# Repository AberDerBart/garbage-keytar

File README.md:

# garbage-keytar

Code and design for a keytar made from an old PC keyboard

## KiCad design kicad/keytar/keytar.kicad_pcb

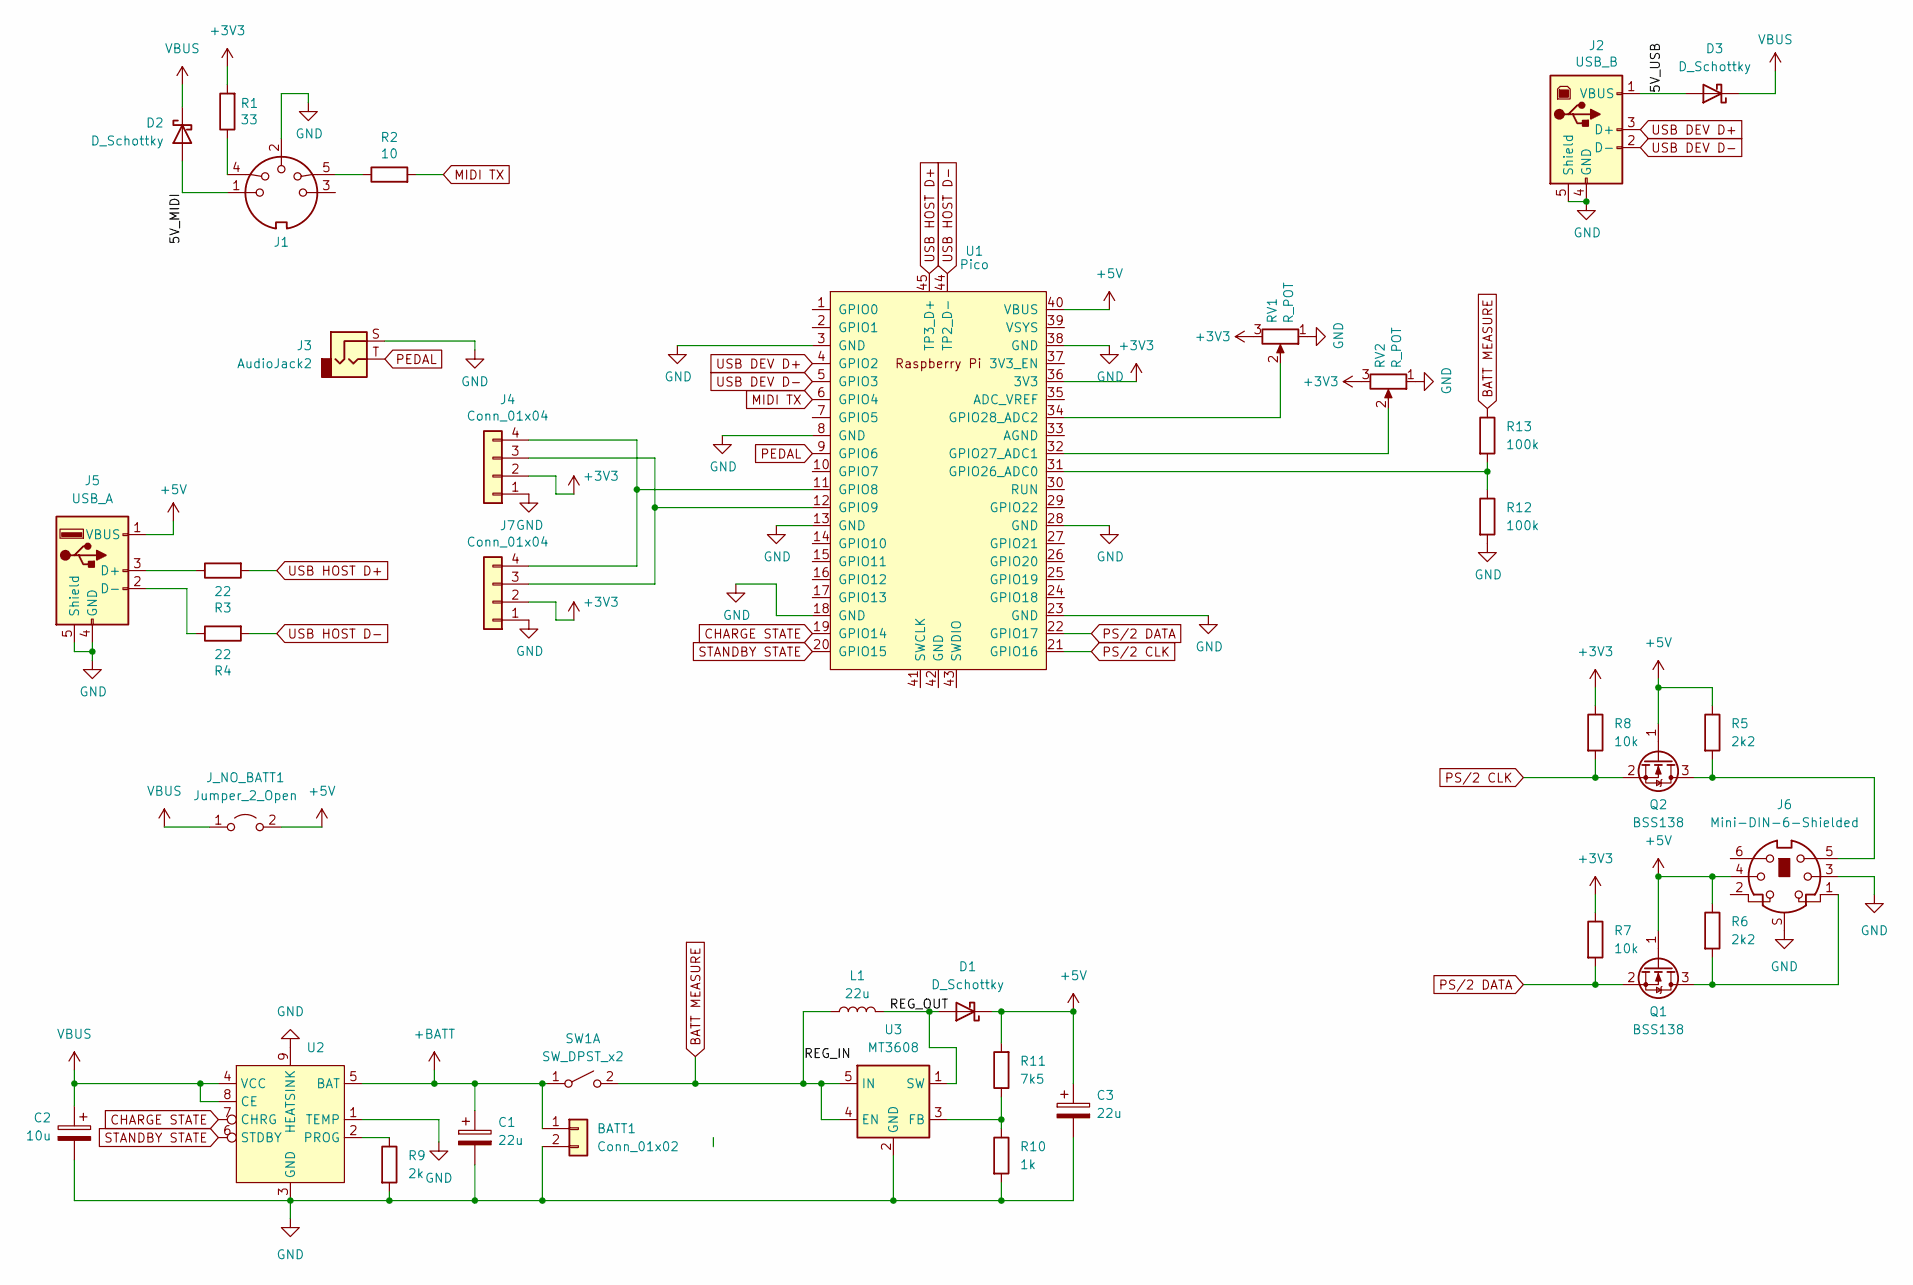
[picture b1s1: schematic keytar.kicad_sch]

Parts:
BATT1: Conn_01x02; JST_XH_B2B-XH-A_1x02_P2.50mm_Vertical
C1, C3: 22u; CP_Elec_4x5.3
C2: 10u; CP_Elec_4x5.3
D1, D2, D3: D_Schottky; D_SMA
J1: MIDI_DIN5
J2: USB_B; USB_B_OST_USB-B1HSxx_Horizontal
J3: AudioJack2; Jack_6.35mm_Neutrik_NRJ4HF_Horizontal
J4, J7: Conn_01x04; JST_XH_B4B-XH-A_1x04_P2.50mm_Vertical
J5: USB_A; USB_A_Molex_67643_Horizontal
J6: Mini-DIN-6-Shielded; EB-DIOS M06
J_NO_BATT1: Jumper_2_Open; SolderJumper-2_P1.3mm_Open_RoundedPad1.0x1.5mm
L1: 22u; L_Bourns-SRN4018
Q1, Q2: BSS138; SOT-23
R1: 33; R_1206_3216Metric_Pad1.30x1.75mm_HandSolder
R2: 10; R_1206_3216Metric_Pad1.30x1.75mm_HandSolder
R3, R4: 22; R_1206_3216Metric_Pad1.30x1.75mm_HandSolder
R5, R6: 2k2; R_1206_3216Metric_Pad1.30x1.75mm_HandSolder
R7, R8: 10k; R_1206_3216Metric_Pad1.30x1.75mm_HandSolder
R9: 2k; R_1206_3216Metric_Pad1.30x1.75mm_HandSolder
R10: 1k; R_1206_3216Metric_Pad1.30x1.75mm_HandSolder
R11: 7k5; R_1206_3216Metric_Pad1.30x1.75mm_HandSolder
R12, R13: 100k; R_1206_3216Metric_Pad1.30x1.75mm_HandSolder
RV1, RV2: R_POT; JST_XH_B3B-XH-A_1x03_P2.50mm_Vertical
SW1: SW_DPST_x2; JST_XH_B3B-XH-A_1x03_P2.50mm_Vertical
U1: Pico; RPi_Pico_debug_hole_USB_SMD_TH
U2: HSOP-8-1EP_3.9x4.9mm_P1.27mm_EP2.3x2.3mm
U3: MT3608; SOT-23-6

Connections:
+3V3: J4.2, J7.2, R1.2, R7.1, R8.1, RV1.3, RV2.3, U1.36 (3V3)
+5V: C3.1, D1.1 (K), J5.1 (VBUS), J6.4, J_NO_BATT1.2 (B), Q1.1 (G), Q2.1 (G), R5.1, R6.1, R11.2, U1.40 (VBUS)
+BATT: BATT1.1, C1.1, SW1.1 (A), U2.5 (BAT)
/5V_MIDI: D2.2 (A), J1.1
/5V_USB: D3.2 (A), J2.1 (VBUS)
/REG_OUT: D1.2 (A), L1.2, U3.1 (SW)
BATT MEASURE: L1.1, R13.1, SW1.2 (B), U3.4 (EN), U3.5 (IN)
CHARGE STATE: U1.19 (GPIO14), U2.7 (CHRG)
GND: BATT1.2, C1.2, C2.2, C3.2, J1.2, J2.4 (GND), J2.5 (Shield), J3.S, J4.1, J5.4 (GND), J5.5 (Shield), J6.3, J6.S, J7.1, R9.2, R10.2, R12.2, RV1.1, RV2.1, U1.3 (GND), U1.8 (GND), U1.13 (GND), U1.18 (GND), U1.23 (GND), U1.28 (GND), U1.38 (GND), U2.1 (TEMP), U2.3 (GND), U2.9 (HEATSINK), U3.2 (GND)
MIDI TX: R2.2, U1.6 (GPIO4)
unnamed: J1.4, R1.1
unnamed: J1.5, R2.1
unnamed: J4.3, J7.3, U1.12 (GPIO9)
unnamed: J4.4, J7.4, U1.11 (GPIO8)
unnamed: J5.3 (D+), R3.1
unnamed: J5.2 (D-), R4.1
unnamed: J6.1, Q1.3 (D), R6.2
unnamed: J6.5, Q2.3 (D), R5.2
unnamed: R12.1, R13.2, U1.31 (GPIO26_ADC0)
unnamed: RV2.2, U1.32 (GPIO27_ADC1)
unnamed: RV1.2, U1.34 (GPIO28_ADC2)
unnamed: R9.1, U2.2 (PROG)
unnamed: R10.1, R11.1, U3.3 (FB)
PEDAL: J3.T, U1.9 (GPIO6)
PS/2 CLK: Q2.2 (S), R8.2, U1.21 (GPIO16)
PS/2 DATA: Q1.2 (S), R7.2, U1.22 (GPIO17)
STANDBY STATE: U1.20 (GPIO15), U2.6 (STDBY)
USB DEV D+: J2.3 (D+), U1.4 (GPIO2)
USB DEV D-: J2.2 (D-), U1.5 (GPIO3)
USB HOST D+: R3.2, U1.45 (TP3_D+)
USB HOST D-: R4.2, U1.44 (TP2_D-)
VBUS: C2.1, D2.1 (K), D3.1 (K), J_NO_BATT1.1 (A), U2.4 (VCC), U2.8 (CE)

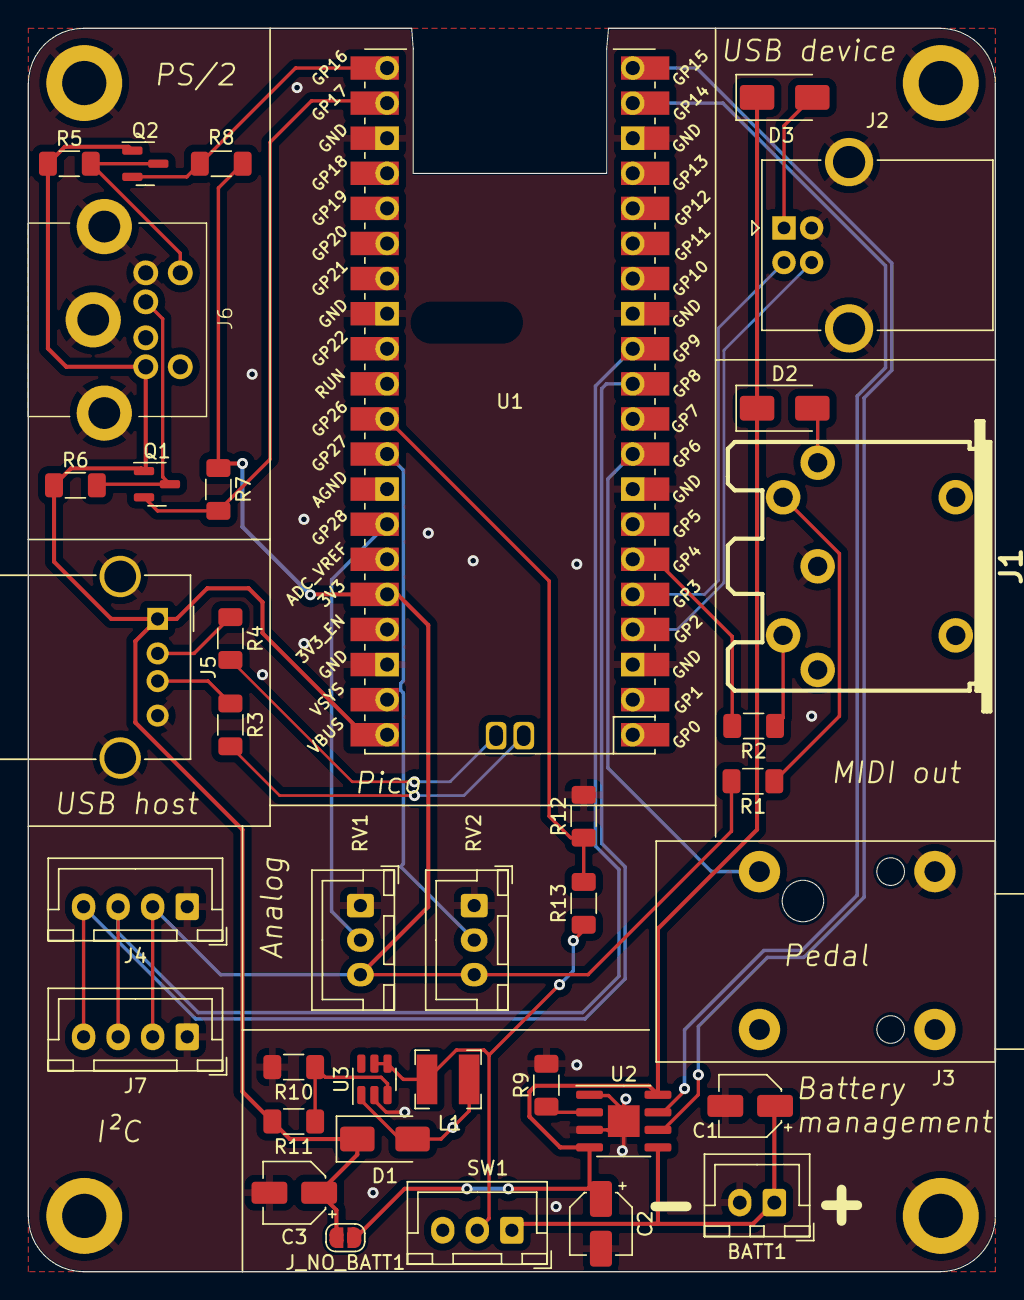
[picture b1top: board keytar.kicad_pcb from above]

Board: 2 copper layers, 70.0 x 90.0 mm, 37 parts (0 on the bottom side), 32 nets.

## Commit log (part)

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2021-04-21 implement MIDI via serial
2021-04-21 implement usb host
2021-04-21 combine keyboard and midi
2021-04-21 implement noteoff events
2021-04-23 add pico_sdk_import
2021-04-24 cad numblock cover
2021-04-24 add makefile
2021-04-24 implement control values with potentiometers
2021-04-24 add gitignore
2021-04-24 add openocd to shell.nix
2021-04-24 cleanup
2021-04-24 improve control value debounce
2021-04-24 rename main source file and binary
2021-04-24 add < key
2021-06-13 improve case
2021-08-19 use pico-sdk in submodule
2021-08-19 re-activate pitchbend
2021-08-19 add pcb
2021-08-19 only report pitchbend on change
2021-09-05 add pico-ssd1306 submodule
2021-09-05 disabled control values
2021-09-05 WIP: adjust pitchbend
2021-09-05 WIP: adapt shell.nix to nixos 21.05
2021-09-05 properly implement PCB
2021-09-05 ignore gerber files
2021-09-05 fix shell.nix, pin nixpkgs
2021-09-05 implement note offset
2021-09-05 implement debug display
2021-10-26 add power via MIDI to pcb
2023-10-01 migrate to flakes and vscode
2023-10-01 fix arrow keys causing midi notes
2023-10-01 formatting
2023-10-01 add program change
2023-10-03 directly include RP_Silicon_KiCad
2023-10-03 clean up
2023-10-03 upgrade pico sdk
2023-10-03 clean up main
2023-10-03 migrate to pio usb
2023-10-03 improve debug messages
2023-10-09 add BLE config to CMakeLists
2023-10-11 add bt example
2023-10-11 simplify code
2023-10-12 make discoverable midi device
2023-10-28 improve logging
2023-10-28 add minicom
2023-10-28 send bluetooth messages along with midi messages
2023-10-28 add bt midi library
2023-10-28 add pico-w-ble-midi-lib
2023-10-28 get midi message spam to work
2023-10-28 clean up init procedure
2023-10-28 display: handle missing display
2023-10-28 route board
2023-10-28 shrink PCB, add USB and PS/2 ports
2023-10-28 update display
2023-10-28 adjust midi pin
2023-10-28 improve pcb
2023-10-28 WIP: redesign pcb
2023-10-28 clean up midi handling
2023-10-28 add battery management
2023-10-28 ignore img folder
2023-11-01 fix deadlock
2023-11-03 kicad: finalize pcb design for order
2024-01-03 add enclosure
2024-01-03 add right half of case
2024-01-03 fine-tune keyboard dimensions
2024-01-03 add space for support strips
2024-01-03 adjust keyboard dimensions
2024-01-03 enclosure: split top and bottom pieces
2024-01-03 increase cable box size
2024-01-03 add wiggleroom for pedal connector
2024-01-03 case finishing touches
2024-01-03 adjust cable channel
2024-01-03 redesign pcb
2024-01-03 remove old casemod
2024-01-03 remove legacy shell.nix
2024-01-03 rename kicad to pcb
2024-01-03 firmware: remove unused code
2024-01-03 move firmware to firmware subfolder
2024-03-14 kicad: use proper capacitors
2024-03-14 add traces to read charger status
2024-03-14 pcb: adjust midi and pedal pins
2024-03-14 pcb: switch usb device and host pins
2024-03-14 fix uart midi pin (code only)
2024-03-14 fix keyboard debug messages
2024-03-14 fix pico-ssd1306 submodule
2024-03-14 add gdb make targets
2024-03-14 re-enable display updates
2024-03-14 rotate display
2024-03-14 fix pico-sdk submodule
2024-03-14 WIP: redesign display
    TODO: adjust build pipeline
    TODO: reintegrate transposition and instrument display
2024-03-14 firmware: try to fix deadlock
2024-03-14 revert to hardware USB host
2024-03-14 firmware: add dev graphics
2024-03-14 firmware: build bin2c tool using nix
2024-07-30 firmware: fix # key
2024-07-31 firmware: implement accordion mappings
2024-07-31 implement piano note lookup using positions
2024-08-01 firmware: display key mapping
2024-08-04 firmware: fix image inversion
2024-08-04 firmware: improve keyboard layout icons
2024-08-04 firmware: fix . and , key swap
2024-08-04 fix offset for chromatic keyboards
2024-08-04 firmware: (partly) fix language server errors
2024-08-04 firmware: implement key layout switch
2024-09-19 add case for switch
2024-09-19 adjust display window
2024-09-19 create debug case
2024-09-20 case: add captive nuts for strap mounts
2025-01-05 firmware: upgrade pic-w-ble-midi-lib
2025-01-05 firmware: format
2025-01-05 enclosure: WIP extract head to own file
2025-01-05 firmware: fix compile warning
2025-01-05 firmware: add BLE client capability
2025-01-05 firmware: implement simple menu system
2025-01-05 firmware: extract menu navigation functions to own files
2025-01-05 firmware: add actions to menu entries
2025-01-05 add menu entries to enable and disable bluetooth
2025-01-05 firmware: start scanning on client activation
2025-01-06 firmware: list BLE MIDI devices in menu
2025-01-06 firmware: implement connecting to bluetooth devices
2025-01-07 firmware: add guitar keymap
2025-01-11 firmware: implement pitchbend
2025-01-12 firmware: activate and fix pitchbend
2025-02-21 enclosure: add neck
2025-02-22 firmware: add envelope menu entry
2025-02-25 firmware: store some config params in flash
2025-02-26 kicad: add voltage divider for battery voltage measurement
2025-03-03 firmware: implement battery state display
2025-03-05 firmware: add histeresis to battery display
2025-03-10 firmware: fix guitar and piano keymaps
2025-03-10 firmware: introduce ble_state
2025-03-10 firmware: implement saving ble state
2025-03-10 firmware: adjust battery threshold
2025-03-12 firmware: fix ble display for client mode
2025-07-22 firmware: refactor UI code
2025-07-22 firmware: rerender ui on status change
2025-07-22 firmware: vscode settings changes
2025-07-22 add notes
2025-08-05 firmware: simplify menu initialization
2025-08-05 move menu to ui subfolder and add free function to menu_item_t
2025-08-05 firmware: allow to navigate menu items left and right
2025-08-05 firmware: make ui render function more flexible
2025-08-05 build menu items on the heap as ui_element_t
2025-08-06 firmware: add ui_menu_item_uint8_t
2025-08-06 firmware: add focus flag to ui render function
2025-08-06 firmware: ssd1306_show consistently on end of render
2025-08-06 firmware: move ui files to ui subfolder
2025-08-10 firmware: send adsr settings on bluetooth connection
2025-08-10 implement basic profiles
    currently only properly support envelopes
2025-08-10 firmware: extract menu_add_envelope_entries function
2025-08-31 firmware: change keymap via select menu item
2025-08-31 firmware: only show applicable arrows for menu uint8 and select items
2025-10-23 firmware: add primitive omnichord layout
